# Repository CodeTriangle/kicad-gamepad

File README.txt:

Engineer: Richard Snider
lighthousemaniac@gmail.com
801-512-4541

Please contact me about any issues. This is my first time submitting a PCB for
printing, so there are likely problems.

EDA Suite: KiCad 9

PCB:
Conformal coating: no
ISO 13458 assembly requirement: no
Soldermask (no color preference): top and bottom
White silkscreen: top and bottom
Material type: FR4
Lead-free process
Copper weight: 1.2oz or approximate equivalent

Gerber format: 4.6, Protel standard naming
Component placement (metric measurements): controller-top.pos, controller-bottom.pos
Component BOM: controller.csv

Notes:
All placeable parts in BOM are available on DigiKey.
Parts marked with DNP will be sourced by me.

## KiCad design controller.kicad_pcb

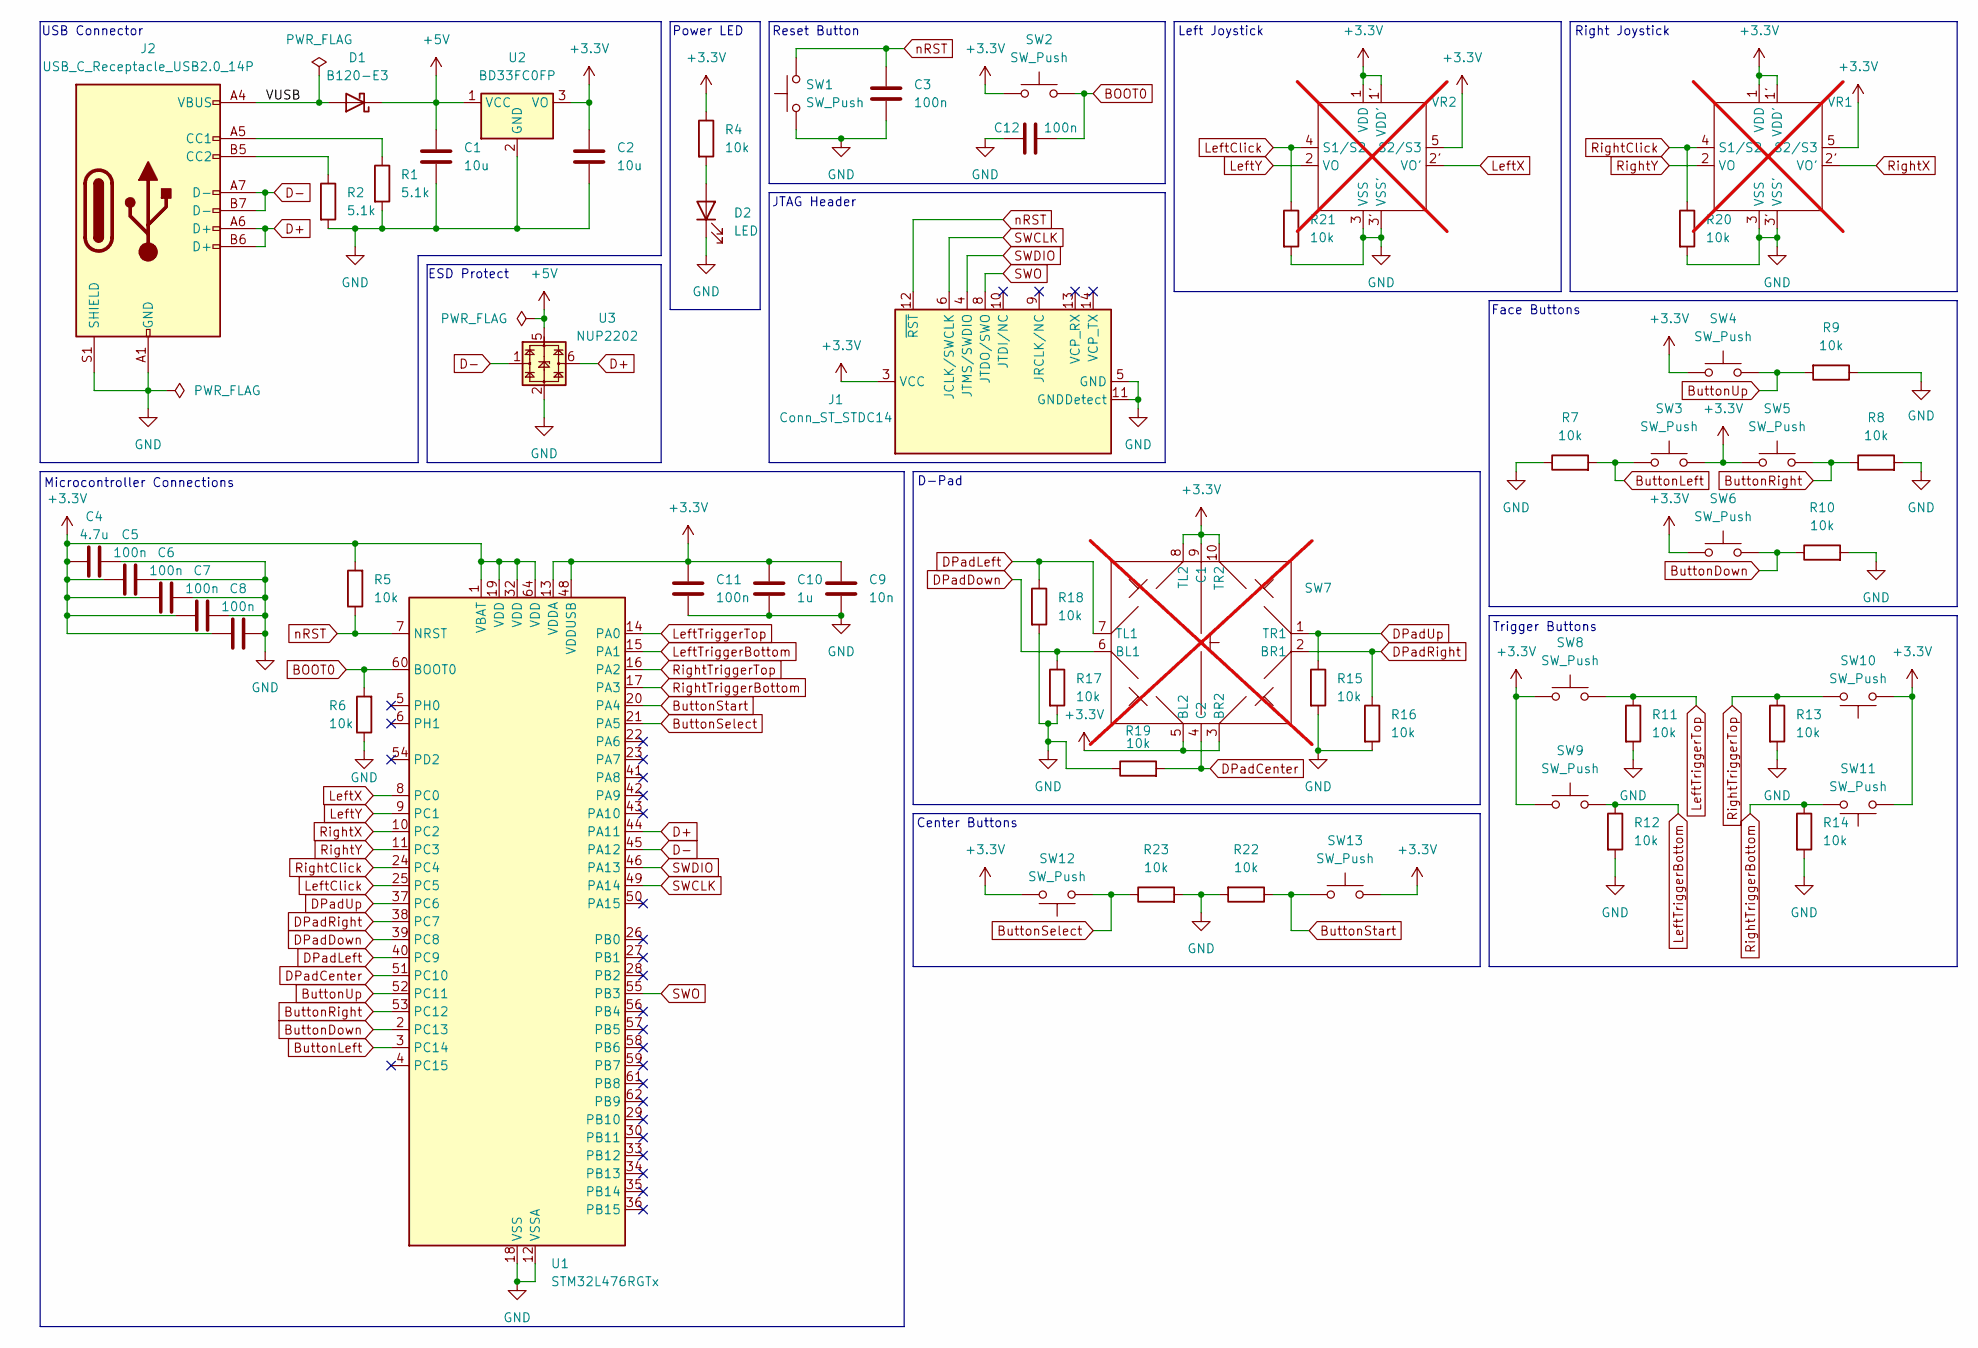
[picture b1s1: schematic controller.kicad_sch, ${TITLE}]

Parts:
C1, C2: 10u; C_0402_1005Metric; MPN GRM155R61A106ME11D
C3, C5, C6, C7, C8, C11, C12: 100n; C_0201_0603Metric; MPN GRM033C71C104KE14D
C4: 4.7u; C_0201_0603Metric; MPN GRM035R60J475ME15D
C9: 10n; C_0201_0603Metric; MPN GRM033R71A103KA01D
C10: 1u; C_0201_0603Metric; MPN CL03A105MQ3CSNC
D1: B120-E3; D_SMA; MPN B120-E3/61T
D2: LED; LED_0201_0603Metric; MPN CSP0603AN101-WP30300563001-3T
J1: Conn_ST_STDC14; CONN14_3220-14_CNC; MPN 3220-14-0100-00
J2: USB_C_Receptacle_USB2.0_14P; USB_C_Receptacle_GCT_USB4085; MPN USB4085-GF-A
R1, R2: 5.1k; R_0201_0603Metric; MPN RC0201FR-075K1L
R4, R5, R6, R7, R8, R9, R10, R11, R12, R13, R14, R15, R16, R17, R18, R19, R20, R21, R22, R23: 10k; R_0201_0603Metric; MPN CRCW020110K0FNED
SW1, SW2: SW_Push; SW_Push_1P1T_NO_CK_KMR2; MPN Y78B21110FP
SW3, SW4, SW5, SW6: SW_Push; SW_Push_1P1T_NO_CK_PTS125Sx43SMTR; MPN 10913247
SW7: K1-1210UN-01; not fitted
SW8, SW9, SW10, SW11: SW_Push; SW_EVQ-P7A01P_Single; MPN EVQ-P7A01P
SW12, SW13: SW_Push; SW_PUSH_6mm; MPN 1301.9302
U1: STM32L476RGTx; LQFP-64_10x10mm_P0.5mm; MPN STM32L476RGT6
U2: BD33FC0FP; TO-252-2; MPN BD33FC0FP-E2
U3: NUP2202; SOT-363_SC-70-6; MPN NUP2202W1T2G
VR1, VR2: 3D16A1N; not fitted

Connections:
+3.3V: C2.2, C4.2, C5.1, C6.1, C7.1, C8.1, C9.2, C10.2, C11.2, J1.3 (VCC), R4.1, R5.2, SW2.1, SW3.2, SW4.1, SW5.1, SW6.1, SW7.3 (BR2), SW7.5 (BL2), SW7.8 (TL2), SW7.9 (C1), SW7.10 (TR2), SW8.1, SW9.1, SW10.1, SW11.1, SW12.2, SW13.2, U1.1 (VBAT), U1.13 (VDDA), U1.19 (VDD), U1.32 (VDD), U1.48 (VDDUSB), U1.64 (VDD), U2.3 (VO), VR1.1 (VDD), VR1.1' (VDD'), VR1.5 (S2/S3), VR2.1 (VDD), VR2.1' (VDD'), VR2.5 (S2/S3)
+5V: C1.1, D1.1 (K), U2.1 (VCC), U3.5
/VUSB: D1.2 (A), J2.A4 (VBUS), J2.A9 (VBUS), J2.B4 (VBUS), J2.B9 (VBUS)
BOOT0: C12.1, R6.2, SW2.2, U1.60 (BOOT0)
ButtonDown: R10.1, SW6.2, U1.2 (PC13)
ButtonLeft: R7.2, SW3.1, U1.3 (PC14)
ButtonRight: R8.1, SW5.2, U1.53 (PC12)
ButtonSelect: R23.1, SW12.1, U1.21 (PA5)
ButtonStart: R22.1, SW13.1, U1.20 (PA4)
ButtonUp: R9.2, SW4.2, U1.52 (PC11)
D+: J2.A6 (D+), J2.B6 (D+), U1.44 (PA11), U3.6
D-: J2.A7 (D-), J2.B7 (D-), U1.45 (PA12), U3.1
DPadCenter: R19.2, SW7.4 (C2), U1.51 (PC10)
DPadDown: R17.1, SW7.6 (BL1), U1.39 (PC8)
DPadLeft: R18.1, SW7.7 (TL1), U1.40 (PC9)
DPadRight: R16.1, SW7.2 (BR1), U1.38 (PC7)
DPadUp: R15.1, SW7.1 (TR1), U1.37 (PC6)
GND: C1.2, C2.1, C3.1, C4.1, C5.2, C6.2, C7.2, C8.2, C9.1, C10.1, C11.1, C12.2, D2.1 (K), J1.5 (GND), J1.7 (GND), J1.11 (GNDDetect), J2.A1 (GND), J2.A12 (GND), J2.B1 (GND), J2.B12 (GND), J2.S1 (SHIELD), R1.2, R2.2, R6.1, R7.1, R8.2, R9.1, R10.2, R11.2, R12.2, R13.2, R14.2, R15.2, R16.2, R17.2, R18.2, R19.1, R20.2, R21.2, R22.2, R23.2, SW1.1, U1.12 (VSSA), U1.18 (VSS), U1.31 (VSS), U1.47 (VSS), U1.63 (VSS), U2.2 (GND), U3.2, VR1.3 (VSS), VR1.3' (VSS'), VR2.3 (VSS), VR2.3' (VSS')
LeftClick: R21.1, U1.25 (PC5), VR2.4 (S1/S2)
LeftTriggerBottom: R12.1, SW9.2, U1.15 (PA1)
LeftTriggerTop: R11.1, SW8.2, U1.14 (PA0)
LeftX: U1.8 (PC0), VR2.2' (VO')
LeftY: U1.9 (PC1), VR2.2 (VO)
unnamed: D2.2 (A), R4.2
unnamed: J2.A5 (CC1), R1.1
unnamed: J2.B5 (CC2), R2.1
RightClick: R20.1, U1.24 (PC4), VR1.4 (S1/S2)
RightTriggerBottom: R14.1, SW11.2, U1.17 (PA3)
RightTriggerTop: R13.1, SW10.2, U1.16 (PA2)
RightX: U1.10 (PC2), VR1.2' (VO')
RightY: U1.11 (PC3), VR1.2 (VO)
SWCLK: J1.6 (JCLK/SWCLK), U1.49 (PA14)
SWDIO: J1.4 (JTMS/SWDIO), U1.46 (PA13)
SWO: J1.8 (JTDO/SWO), U1.55 (PB3)
nRST: C3.2, J1.12 (~RST), R5.1, SW1.2, U1.7 (NRST)

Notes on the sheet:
D-Pad
Right Joystick
Trigger Buttons
ESD Protect
Microcontroller Connections
Power LED
JTAG Header
Reset Button
Face Buttons
Left Joystick
Center Buttons
USB Connector

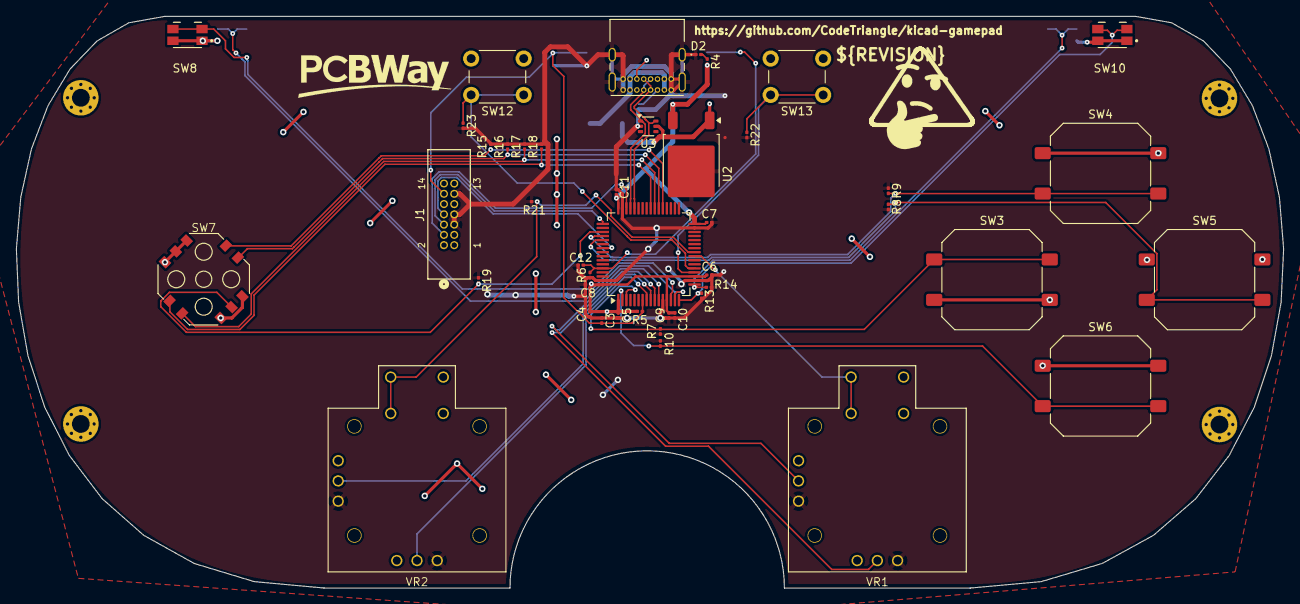
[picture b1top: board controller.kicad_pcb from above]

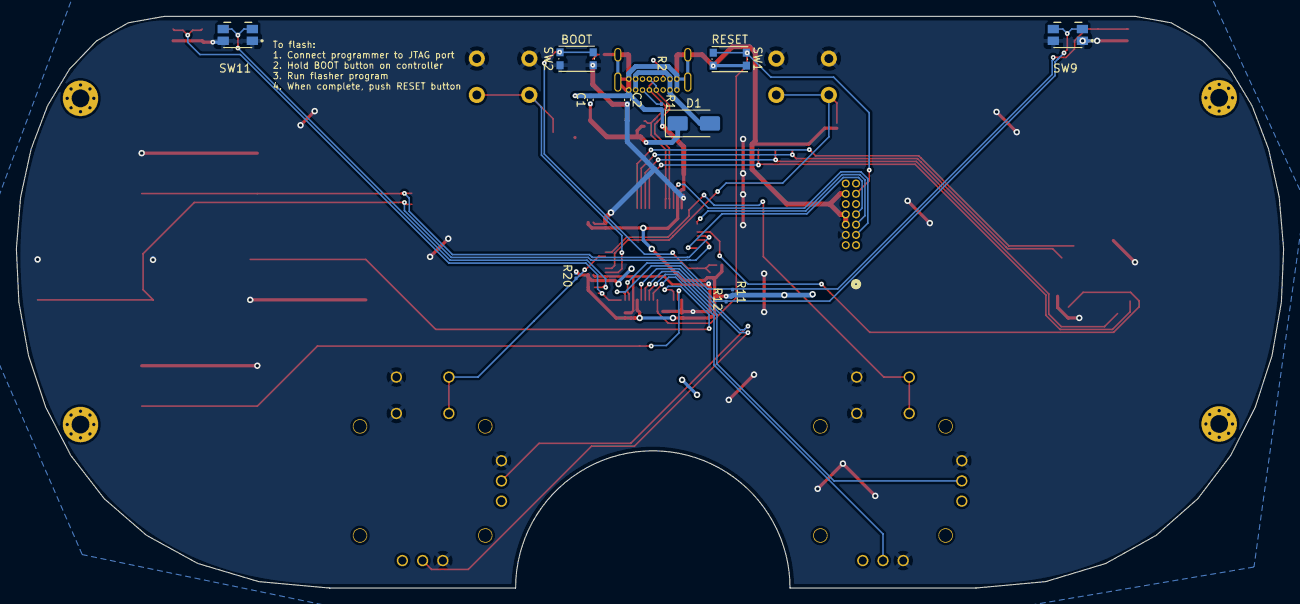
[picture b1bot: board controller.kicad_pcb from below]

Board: 2 copper layers, 156.8 x 70.7 mm, 56 parts (12 on the bottom side), 35 nets.

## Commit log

2025-10-23 place a bunch of components
2025-10-25 initial ground/power routing
2025-10-25 a bit more power routing
2025-10-25 change to receptacle
2025-10-25 fix some DRC checks
2025-10-25 add libraries
2025-10-26 fix pin assignments
2025-10-26 add some control components to schematic and pcb
2025-11-02 finish routing, more or less
2025-11-02 update modules to fix
2025-11-02 fix most drc issues
2025-11-02 add vanity
2025-11-03 add start and select + resistors to all other buttons
2025-11-03 fix ERC and add metadata
2025-11-03 add fabrication files
2025-11-06 set DNP flags
2025-11-13 move symbol and footprint libraries to own folder
2025-11-13 add button and connector components
2025-11-13 add bom numbers
2025-11-13 update pcb to reflect new footprints
2025-11-14 some minor trace changes
2025-11-14 add pcbway logo and some more trace modifications
2025-11-14 change NPTHs on joystick footprint
2025-11-14 pourin
2025-11-14 final commit before i do something really silly
2025-11-14 modify stdc14 connector footprint
2025-11-14 add 3220 component
2025-11-14 change some more tracks
2025-11-14 change symbol properties to new version
2025-11-14 tweak again
2025-11-14 normalize text
2025-11-16 final few fixes; R1.1-A
